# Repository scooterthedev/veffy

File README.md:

# veffy
A Custom VHF Walkie Talkie

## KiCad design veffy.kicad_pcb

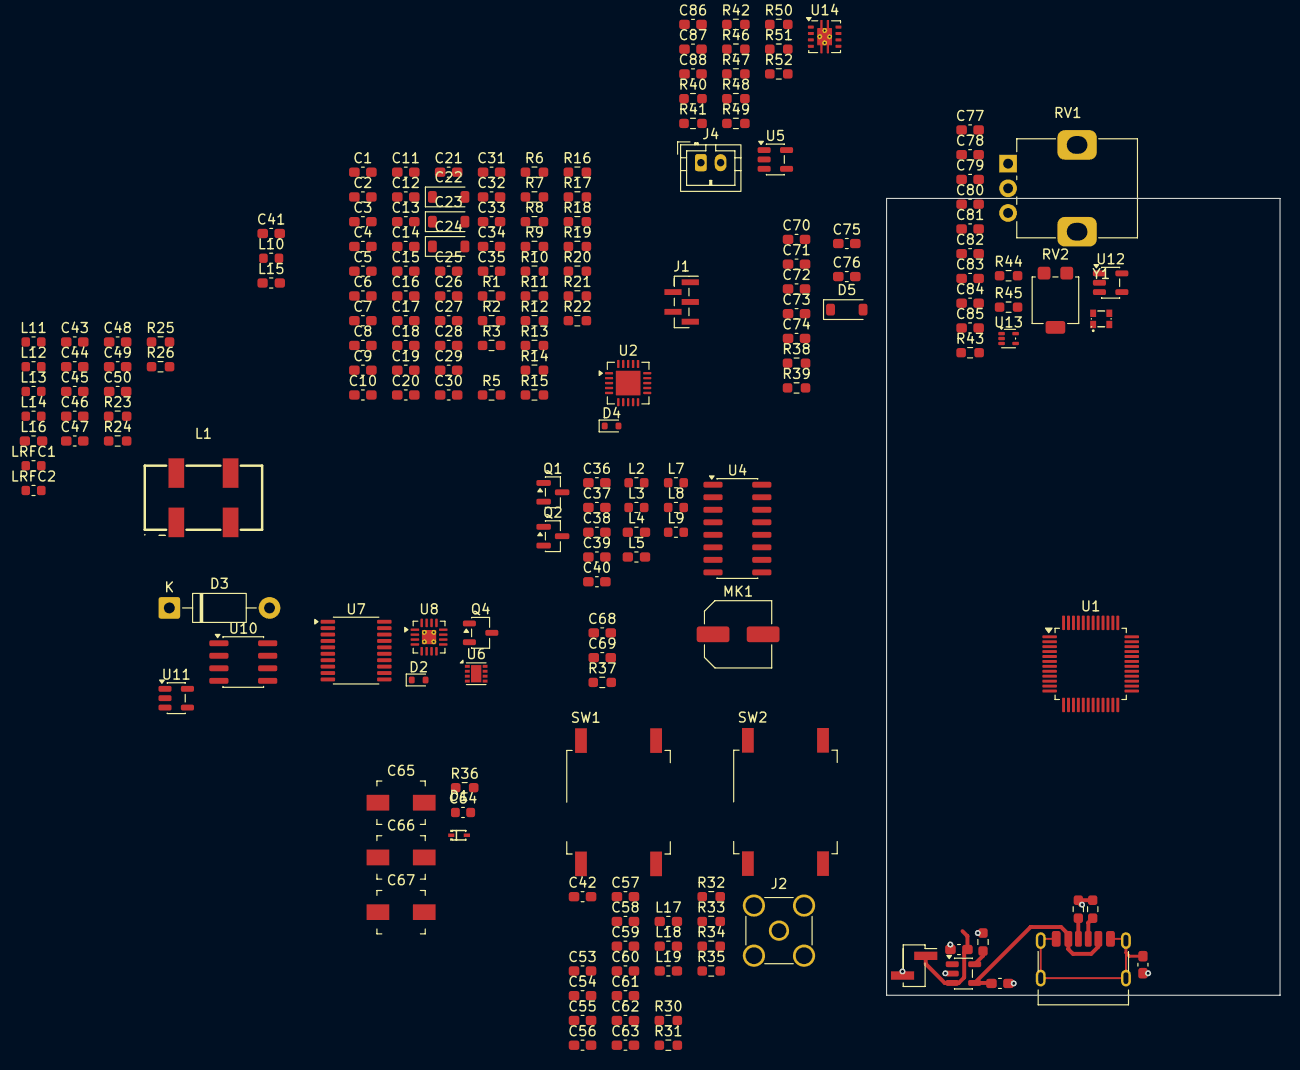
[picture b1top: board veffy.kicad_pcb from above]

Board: 4 copper layers, 39.9 x 80.8 mm, 192 parts (0 on the bottom side), 108 nets.

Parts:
C1, C2, C3, C4, C11, C12, C13, C14, C15, C34, C82, C84: 100nF; C_0603_1608Metric_Pad1.08x0.95mm_HandSolder
C5, C35, C55, C56, C68, C81, C86, C87, C88: 1uF; C_0603_1608Metric_Pad1.08x0.95mm_HandSolder
C6, C8, C27, C29, C36, C38, C39, C41, C73: 100pF; C_0603_1608Metric_Pad1.08x0.95mm_HandSolder
C7: 10pF; C_0603_1608Metric_Pad1.08x0.95mm_HandSolder
C9: 5pF; C_0603_1608Metric_Pad1.08x0.95mm_HandSolder
C10, C16, C17, C18, C30, C31, C32, C37, C45, C75: 0.1uF; C_0603_1608Metric_Pad1.08x0.95mm_HandSolder
C19: 150pF; C_0603_1608Metric_Pad1.08x0.95mm_HandSolder
C20, C44: 10.9pF; C_0603_1608Metric_Pad1.08x0.95mm_HandSolder
C21, C51, C52, C80: 4.7uF; C_0603_1608Metric_Pad1.08x0.95mm_HandSolder
C22, C24: 100nF; D_SOD-123
C23: 1uF; D_SOD-123
C25, C74, C76, C77, C85: 1nF; C_0603_1608Metric_Pad1.08x0.95mm_HandSolder
C26, C28: 15pF; C_0603_1608Metric_Pad1.08x0.95mm_HandSolder
C33, C69, C83: 10nF; C_0603_1608Metric_Pad1.08x0.95mm_HandSolder
C40, C48: 2pF; C_0603_1608Metric_Pad1.08x0.95mm_HandSolder
C42: 5-30pF; C_0603_1608Metric_Pad1.08x0.95mm_HandSolder
C43: 35.4pF; C_0603_1608Metric_Pad1.08x0.95mm_HandSolder
C46, C70, C71: 22pF; C_0603_1608Metric_Pad1.08x0.95mm_HandSolder
C47, C57, C58, C62: 27pF; C_0603_1608Metric_Pad1.08x0.95mm_HandSolder
C49: 56pF; C_0603_1608Metric_Pad1.08x0.95mm_HandSolder
C50: 0.7pF; C_0603_1608Metric_Pad1.08x0.95mm_HandSolder
C53: 1000pF; C_0603_1608Metric_Pad1.08x0.95mm_HandSolder
C54: 470uF; C_0603_1608Metric_Pad1.08x0.95mm_HandSolder
C59: 6.8nF; C_0603_1608Metric_Pad1.08x0.95mm_HandSolder
C60, C61: 0.8pF; C_0603_1608Metric_Pad1.08x0.95mm_HandSolder
C63: 68nF; C_0603_1608Metric_Pad1.08x0.95mm_HandSolder
C64: 1nF; C_0603_1608Metric
C65, C66, C67: 2-10pF; C_Trimmer_Murata_TZB4-A
C72: 100pf; C_0603_1608Metric_Pad1.08x0.95mm_HandSolder
C78: 220nF; C_0603_1608Metric_Pad1.08x0.95mm_HandSolder
C79: 47nF; C_0603_1608Metric_Pad1.08x0.95mm_HandSolder
CN1: XH-2AW_C2908611; PinHeader_1x02_P2.00mm_Vertical_SMD_Pin1Right
D1: SMV1236-079LF; SC-79_L1.2-W0.8-LS1.6-RD
D2, D4: BAR64-02V; D_SOD-523
D3: 1N5819; D_DO-41_SOD81_P10.16mm_Horizontal
D5: 1N4148W; D_SOD-123
FB1: FerriteBead; C_0603_1608Metric_Pad1.08x0.95mm_HandSolder
J1: SWD; PinHeader_1x05_P1.00mm_Vertical_SMD_Pin1Right
J2: Conn_Coaxial; SMA_Amphenol_901-144_Vertical
J3: USB_C_Receptacle_USB2.0_14P; USB_C_Receptacle_HRO_TYPE-C-31-M-17
J4: Conn_01x02; JST_PH_B2B-PH-K_1x02_P2.00mm_Vertical
L1: HCCF2-455.000-LTWCDL; FILTER-SMD_4P-L11.9-W6.5-P5.50-LS7.5-BL
L2: 680uH; L_0603_1608Metric
L3: 47nH; L_0603_1608Metric
L4: 51nH; L_0603_1608Metric_Pad1.05x0.95mm_HandSolder
L5: 390nH; L_0603_1608Metric_Pad1.05x0.95mm_HandSolder
L7: 12nH; L_0603_1608Metric
L8, L9, L10: 13nH; L_0603_1608Metric
L11, L12: 71.5nH; L_0603_1608Metric
L13: 1uH; L_0603_1608Metric
L14: 2.7nH; L_0603_1608Metric
L15: 150uH; L_0603_1608Metric_Pad1.05x0.95mm_HandSolder
L16: 280nH; L_0603_1608Metric_Pad1.05x0.95mm_HandSolder
L17, L18, L19: 0603CS-33NXJLW; L_0603_1608Metric_Pad1.05x0.95mm_HandSolder
LRFC1: 10uH; L_0603_1608Metric
LRFC2: 1uH; L_0603_1608Metric
MK1: MIC_IN; C_Elec_6.3x5.4
Q1: AO3401A; SOT-23
Q2: BFR93A; SOT-23
Q4: BFR93AE6327HTSA1; SOT-23-3
R1, R9, R12, R24, R25, R30, R51, R52: 10K; R_0603_1608Metric_Pad0.98x0.95mm_HandSolder
R2, R38: 4.7K; R_0603_1608Metric_Pad0.98x0.95mm_HandSolder
R3, R10: 2.2K; R_0603_1608Metric_Pad0.98x0.95mm_HandSolder
R5, R8, R17, R19, R47, R48: 100K; R_0603_1608Metric_Pad0.98x0.95mm_HandSolder
R6, R34, R49: 47K; R_0603_1608Metric_Pad0.98x0.95mm_HandSolder
R7, R18, R22, R37: 1K; R_0603_1608Metric_Pad0.98x0.95mm_HandSolder
R11: 330; R_0603_1608Metric_Pad0.98x0.95mm_HandSolder
R13, R41: 6.8K; R_0603_1608Metric_Pad0.98x0.95mm_HandSolder
R14, R15: 200; R_0603_1608Metric_Pad0.98x0.95mm_HandSolder
R16: 150; R_0603_1608Metric_Pad0.98x0.95mm_HandSolder
R20, R44: 33; R_0603_1608Metric_Pad0.98x0.95mm_HandSolder
R21, R23, R26: 1.8K; R_0603_1608Metric_Pad0.98x0.95mm_HandSolder
R27, R28: 5.1K; R_0603_1608Metric_Pad0.98x0.95mm_HandSolder
R29: 2K; R_0603_1608Metric_Pad0.98x0.95mm_HandSolder
R31: 0.62; R_0603_1608Metric_Pad0.98x0.95mm_HandSolder
R32: 1.2K; R_0603_1608Metric_Pad0.98x0.95mm_HandSolder
R33: 3.6K; R_0603_1608Metric_Pad0.98x0.95mm_HandSolder
R35: 3.9K; R_0603_1608Metric_Pad0.98x0.95mm_HandSolder
R36: 680; R_0603_1608Metric_Pad0.98x0.95mm_HandSolder
R39, R50: 470K; R_0603_1608Metric_Pad0.98x0.95mm_HandSolder
R40, R42: 3.3K; R_0603_1608Metric_Pad0.98x0.95mm_HandSolder
R43: 18K; R_0603_1608Metric_Pad0.98x0.95mm_HandSolder
R45: 1M; R_0603_1608Metric_Pad0.98x0.95mm_HandSolder
R46: 20K; R_0603_1608Metric_Pad0.98x0.95mm_HandSolder
RV1: 22K; Potentiometer_Alps_RK09K_Single_Vertical
RV2: 10K; Potentiometer_Bourns_3314G_Vertical
SW1, SW2: SW_Push; SW_MEC_5GSH9
U1: ATSAMD21G18A-A; TQFP-48_7x7mm_P0.5mm
U2: ADF4112BCPZ; QFN-20-1EP_4x4mm_P0.5mm_EP2.5x2.5mm
U4: MC3361; SOIC-16_3.9x9.9mm_P1.27mm
U5: TLV9061xDBV; SOT-23-5
U6: TLV9062IDSGR; DFN-8-1EP_2x2mm_P0.5mm_EP1.05x1.75mm
U7: AD9834; TSSOP-20_4.4x6.5mm_P0.65mm
U8: QPA9510; VQFN-16-1EP_3x3mm_P0.5mm_EP1.45x1.45mm_ThermalVias
U9: MCP73831-2-OT; SOT-23-5
U10: MC34063AD; SOIC-8_3.9x4.9mm_P1.27mm
U11: AP2112K-3.3; SOT-23-5
U12: AP2112K-1.8; SOT-23-5
U13: 74LVC1GU04DRL; SOT-553
U14: TPA6203A1DRB; Texas_DRB0008A
Y1: 26 MHz; OSC-SMD_4P-L2.0-W1.6-BL_EPSON_TG-5006CJ-19H

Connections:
AF_VOL: C24.2, RV1.2
AGND: C1.1, C2.1, C3.1, C4.1, C5.2, C6.1, C7.1, C8.1, C9.1, C10.1, C11.1, C12.1, C13.1, C14.1, C15.1, C16.1, C17.1, C18.1, C20.1, C21.2, C22.2, C23.1, C27.2, C30.2, C31.2, C32.2, C33.2, C34.2, C35.1, C37.2, C40.2, C43.1, C44.1, C45.1, C46.2, C47.2, C48.2, C50.2, C51.1, C52.1, C53.1, C54.1, C55.1, C56.1, C57.2, C58.2, C59.2, C62.2, C63.1, C65.2, C66.2, C67.2, C69.2, C70.2, C71.2, C74.2, C78.2, C80.1, C81.1, C82.1, C84.2, C87.1, C88.1, CN1.2, D2.1 (K), FB1.1, J1.1, J2.2 (Ext), L1.3 (GND), L1.4 (GND), L17.1, L18.1, L19.1, MK1.1 (-), R2.2, R5.2, R10.2, R11.2, R13.2, R14.2, R15.2, R20.2, R22.2, R24.1, R25.1, R27.2, R28.1, R29.1, R32.1, R34.2, R40.2, R48.2, RV1.3, RV2.1, SW1.1, SW2.1, U1.5 (GNDANA), U1.18 (GND), U1.35 (GND), U1.42 (GND), U2.1 (CPGND), U2.2 (AGND@1), U2.3 (AGND@2), U2.9 (DGND@1), U2.10 (DGND@2), U2.21 (EPAD), U4.15 (GND), U5.2 (V-), U6.3 (+), U6.4 (V-), U7.7 (DGND), U7.9 (FSELECT), U7.10 (PSELECT), U7.12 (SLEEP), U7.18 (AGND), U8.2 (GND1), U8.4 (GND2), U8.17 (GND_EP), U9.2 (V_{SS}), U10.2 (SwE), U10.4 (GND), U11.2 (GND), U12.2 (GND), U13.3 (GND), U14.7 (GND), U14.9 (GND), Y1.2 (GND)
AUDIO_OUT: R41.2, R42.2, U4.9 (AF_OUT)
AVDD1: C10.2, C11.2, C12.2, C13.2, C14.2, C15.2, C54.2, D3.1 (K), R33.1, U2.6 (AVDD@1), U2.7 (AVDD@2), U2.11 (CE), U2.16 (DVDD@1), U2.17 (DVDD@2), U2.18 (VP)
BAND_OUT: C39.1, C57.1, C61.1, C67.1, L19.2
BAT+: C52.2, C55.2, CN1.1, L15.2, R31.2, U9.3 (V_{BAT}), U10.6 (Vin), U11.1 (VIN), U11.3 (EN), U14.1 (~SHUTDOWN)
DDS_RST: R12.2, U1.31 (PA22), U7.11 (RESET)
DVDD: C1.2, C2.2, C3.2, C4.2, C16.2, C19.2, C22.1, C26.1, C27.1, C31.1, C32.1, C35.2, C42.2, C56.2, C84.1, J1.2, L2.2, L3.2, L7.2, L8.2, L9.2, L10.2, L13.2, LRFC2.1, Q1.2 (S), Q2.1 (B), R1.2, R3.2, R8.1, R9.1, R12.1, R17.2, R19.2, R21.1, R23.2, R26.2, R30.1, R43.2, R46.2, R47.1, U1.6 (VDDANA), U1.17 (VDDIO), U1.36 (VDDIO), U1.44 (VDDIN), U4.4 (VCC), U5.5 (V+), U6.8 (V+), U7.4 (AVDD), U7.5 (DVDD), U11.5 (VOUT), U12.1 (VIN), U12.3 (EN), U13.5 (VCC)
FILTER_IN: C76.1, R39.1, U4.10 (FILT_IN)
FILTER_OUT: C75.2, C77.1, R39.2, U4.11 (FILTER_OUT)
FSYNC: U1.28 (PA19), U7.15 (~FSYNC)
GPIO_CS: U1.27 (PA18), U2.14 (LE)
IF_455K: C58.1, C60.2, C65.1, L1.1 (Input), L17.2
IF_OUT: L1.2 (Output), U4.5 (LIM_IN)
INPUTB: C7.2, C64.2, R36.1
LC: C19.1, C42.1, L2.1, R46.1, U4.8 (QUADRATURE_INPUT)
MCLK: R44.2, U7.8 (MCLK)
MIC_PREAMP: C68.2, R5.1, R8.2, U6.5 (+)
MOSI: U1.25 (PA16), U2.13 (DATA), U7.13 (SDATA)
MUTE: C79.2, RV1.1, U4.14 (MUTE)
unnamed: C17.2, U4.6 (DEC1)
unnamed: C18.2, U4.7 (DEC1)
unnamed: C21.1, R7.2
unnamed: C24.1, R49.1
unnamed: C37.1, Q4.2 (E), R20.1
unnamed: C38.1, LRFC2.2, Q4.3 (C)
unnamed: C39.2, Q4.1 (B), R21.2, R22.1
unnamed: C43.2, L11.2, L12.1
unnamed: C46.1, C48.1, C49.1, L14.2
unnamed: C60.1, C61.2, C62.1, C66.1, L18.2
unnamed: C63.2, R35.1
unnamed: C74.1, L5.1, R16.2
unnamed: C76.2, C77.2, R40.1, R41.1
unnamed: C78.1, C79.1, R42.1
unnamed: C83.2, R45.1, U13.2
unnamed: C85.2, R44.1, R45.2, U13.4
unnamed: C86.1, R51.2
unnamed: C86.2, R50.2, U5.1
unnamed: C87.2, R52.1
unnamed: C28.2, D1.2 (A), R34.1
unnamed: D1.1 (K), LRFC1.1
unnamed: C70.1, C72.1, D2.2 (A), L4.2
unnamed: C73.1, D4.2 (A), L5.2
unnamed: C36.2, C71.1, D4.1 (K), L4.1
unnamed: D5.2 (A), R18.1
unnamed: C75.1, D5.1 (K), R38.1
unnamed: C36.1, J2.1 (In)
unnamed: J3.A5 (CC1), R28.2
unnamed: J3.B5 (CC2), R27.1
unnamed: FB1.2, J3.A12 (GND), J3.B12 (GND), J3.SH (SHIELD)
unnamed: L9.1, U8.6 (VCC2)
unnamed: L10.1, U8.5 (VCC2)
unnamed: C68.1, MK1.2 (+), R3.1
unnamed: Q1.3 (D), R16.1
unnamed: C26.2, C28.1, C29.2, L3.1, Q2.3 (C)
unnamed: Q2.2 (E), R11.1
unnamed: R9.2, R10.1
unnamed: R14.1, R36.2
unnamed: R38.2, RV2.2
unnamed: R43.1, RV2.3
unnamed: C69.1, R37.2, U1.9 (PA04)
unnamed: R30.2, SW2.2, U1.24 (PA15)
unnamed: C5.1, U1.43 (VDDCORE)
unnamed: C6.2, U2.4 (RFINB)
unnamed: R2.1, U2.19 (RSET)
unnamed: C23.2, R47.2, R48.1, U5.3 (+)
unnamed: R49.2, R50.1, U5.4 (-)
unnamed: U6.1, U6.2 (-)
unnamed: C25.1, R6.1, R7.1, U6.6 (-)
unnamed: C34.1, U7.6 (CAP/2.5V)
unnamed: C30.1, U7.3 (COMP)
unnamed: R13.1, U7.1 (FS_ADJUST)
unnamed: C64.1, U7.19 (IOUT)
unnamed: R15.1, U7.20 (IOUTB)
unnamed: C33.1, U7.2 (REFOUT)
unnamed: C40.1, U8.8 (2F0)
unnamed: R23.1, R24.2, U8.16 (APC1)
unnamed: R25.2, R26.1, U8.15 (APC2)
unnamed: C41.2, U8.3 (RFIN)
unnamed: L7.1, U8.1 (VCC1)
unnamed: L8.1, U8.14 (VCC_BIAS)
unnamed: R29.2, U9.5 (PROG)
unnamed: R31.1, U10.7 (Ipk)
unnamed: C53.2, U10.3 (TC)
unnamed: R32.2, R33.2, U10.5 (Vfb)
unnamed: C81.2, C82.2, U12.5 (VOUT), Y1.4 (VDD)
unnamed: C88.2, U14.2 (BYPASS)
unnamed: R51.1, U14.3 (IN+)
unnamed: R52.2, U14.4 (IN-)
unnamed: C83.1, Y1.3 (OUT)
PA_DIE_OUT: C47.1, L13.1, L14.1, U8.9 (RF_OUT), U8.10 (RF_OUT), U8.11 (RF_OUT), U8.12 (RF_OUT)
PA_INT: C38.2, C41.1
PRE_AMP: C25.2, R6.2, R37.1, U6.7
REFIN: C85.1, U2.8 (REFIN)
RST: J1.3, R1.1, SW1.2, U1.40 (~RESET)
RX_MIX_INT: C50.1, L16.2
RX_RF: C72.2, L16.1
SCK: U1.26 (PA17), U2.12 (CLK), U7.14 (SCLK)
SQUELCH_IN: C80.2, R18.2, R19.1, U4.12 (SQ_IN)
SWCLK: J1.4, U1.45 (PA30)
SWIO: J1.5, U1.46 (PA31)
SwC: D3.2 (A), L15.1, U10.1 (SwC), U10.8 (DC)
TX_BAND_INT: C20.2, C49.2, L11.1
TX_EN: Q1.1 (G), R17.1, U1.22 (PA13)
TX_UPCNVRT_OUT: C44.2, C73.2, L12.2
VBUS: C45.2, C51.2, J3.A9 (VBUS), J3.B9 (VBUS), U9.4 (V_{DD})
VCO_OUT: C9.2, C29.1, U2.5 (RFINA)
VTUNE_IN: C59.1, LRFC1.2, R35.2, U2.20 (CP)
